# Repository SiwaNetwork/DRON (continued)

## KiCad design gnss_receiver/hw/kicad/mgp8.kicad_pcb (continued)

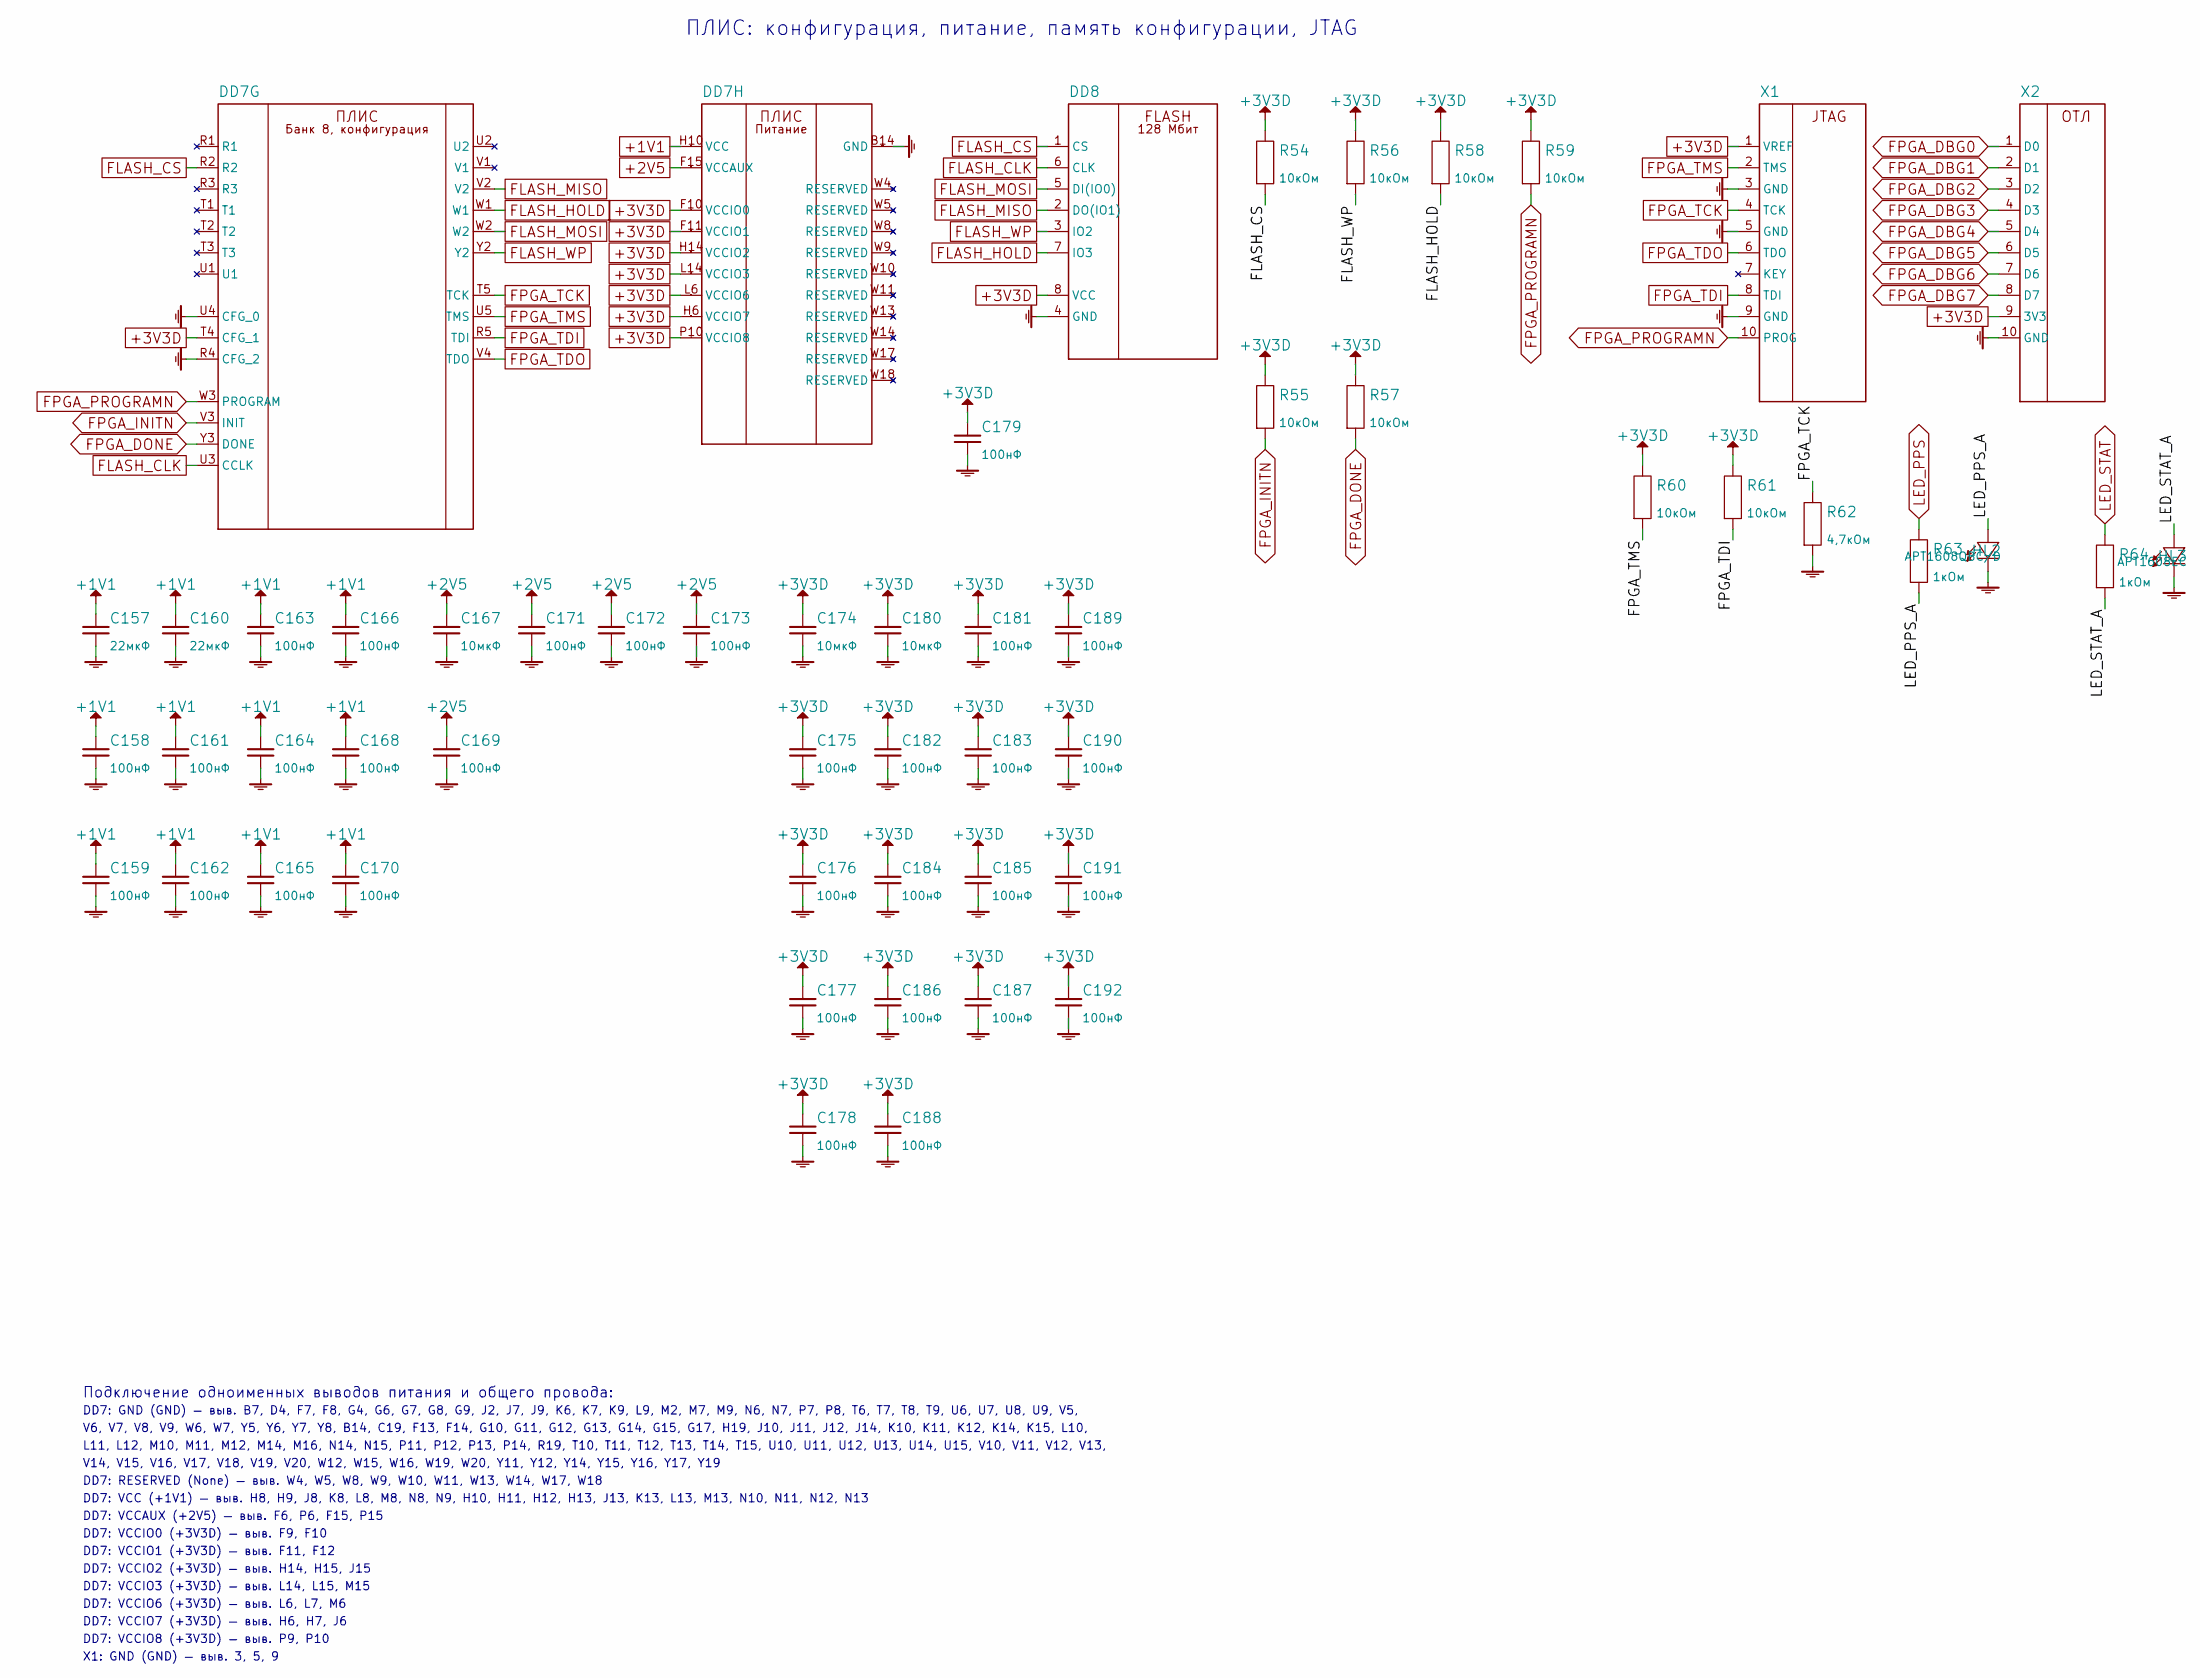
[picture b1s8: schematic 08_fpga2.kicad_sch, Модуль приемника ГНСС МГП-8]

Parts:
C157, C160: 22мкФ; C_0603_1608Metric
C158, C159, C161, C162, C163, C164, C165, C166, C168, C169, C170, C171, C172, C173, C175, C176, C177, C178, C179, C181, C182, C183, C184, C185, C186, C187, C188, C189, C190, C191, C192: 100нФ; C_0402_1005Metric
C167, C174, C180: 10мкФ; C_0603_1608Metric
DD7: LFE5U-45F-6BG381I; Lattice_caBGA-381_17x17mm_Layout20x20_P0.8mm
DD8: W25Q128JVSIQ; SOIC-8_5.3x5.3mm_P1.27mm
HL2: APT1608QBC/D; LED_0603_1608Metric
HL3: APT1608EC; LED_0603_1608Metric
R54, R55, R56, R57, R58, R59, R60, R61: 10кОм; R_0402_1005Metric
R62: 4,7кОм; R_0402_1005Metric
R63, R64: 1кОм; R_0402_1005Metric
X1, X2: FTSH-105-01-L-DV-K; PinHeader_2x05_P1.27mm_Vertical_SMD

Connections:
+1V1: C157.1, C158.1, C159.1, C160.1, C161.1, C162.1, C163.1, C164.1, C165.1, C166.1, C168.1, C170.1, DD7.H8, DD7.H9, DD7.H10 (VCC), DD7.H11, DD7.H12, DD7.H13, DD7.J8, DD7.J13, DD7.K8, DD7.K13, DD7.L8, DD7.L13, DD7.M8, DD7.M13, DD7.N8, DD7.N9, DD7.N10, DD7.N11, DD7.N12, DD7.N13; also elsewhere on the board
+2V5: C167.1, C169.1, C171.1, C172.1, C173.1, DD7.F6, DD7.F15 (VCCAUX), DD7.P6, DD7.P15; also elsewhere on the board
+3V3D: C174.1, C175.1, C176.1, C177.1, C178.1, C179.1, C180.1, C181.1, C182.1, C183.1, C184.1, C185.1, C186.1, C187.1, C188.1, C189.1, C190.1, C191.1, C192.1, DD7.F9, DD7.F10 (VCCIO0), DD7.F11 (VCCIO1), DD7.F12, DD7.H6 (VCCIO7), DD7.H7, DD7.H14 (VCCIO2), DD7.H15, DD7.J6, DD7.J15, DD7.L6 (VCCIO6), DD7.L7, DD7.L14 (VCCIO3), DD7.L15, DD7.M6, DD7.M15, DD7.P9, DD7.P10 (VCCIO8), DD7.T4 (CFG_1), DD8.8 (VCC), R54.1, R55.1, R56.1, R57.1, R58.1, R59.1, R60.1, R61.1, X1.1 (VREF), X2.9 (3V3); also elsewhere on the board
/Лист 8. ПЛИС: конфигурация, питание, память конфигурации, JTAG/LED_PPS_A: HL2.2, R63.2
/Лист 8. ПЛИС: конфигурация, питание, память конфигурации, JTAG/LED_STAT_A: HL3.2, R64.2
FLASH_CLK: DD7.U3 (CCLK), DD8.6 (CLK)
FLASH_CS: DD7.R2, DD8.1 (CS), R54.2
FLASH_HOLD: DD7.W1, DD8.7 (IO3), R58.2
FLASH_MISO: DD7.V2, DD8.2 (DO(IO1))
FLASH_MOSI: DD7.W2, DD8.5 (DI(IO0))
FLASH_WP: DD7.Y2, DD8.3 (IO2), R56.2
FPGA_DBG0: X2.1 (D0); also elsewhere on the board
FPGA_DBG1: X2.2 (D1); also elsewhere on the board
FPGA_DBG2: X2.3 (D2); also elsewhere on the board
FPGA_DBG3: X2.4 (D3); also elsewhere on the board
FPGA_DBG4: X2.5 (D4); also elsewhere on the board
FPGA_DBG5: X2.6 (D5); also elsewhere on the board
FPGA_DBG6: X2.7 (D6); also elsewhere on the board
FPGA_DBG7: X2.8 (D7); also elsewhere on the board
FPGA_DONE: DD7.Y3 (DONE), R57.2; also elsewhere on the board
FPGA_INITN: DD7.V3 (INIT), R55.2; also elsewhere on the board
FPGA_PROGRAMN: DD7.W3 (PROGRAM), R59.2, X1.10 (PROG); also elsewhere on the board
FPGA_TCK: DD7.T5 (TCK), R62.1, X1.4 (TCK)
FPGA_TDI: DD7.R5 (TDI), R61.2, X1.8 (TDI)
FPGA_TDO: DD7.V4 (TDO), X1.6 (TDO)
FPGA_TMS: DD7.U5 (TMS), R60.2, X1.2 (TMS)
GND: C157.2, C158.2, C159.2, C160.2, C161.2, C162.2, C163.2, C164.2, C165.2, C166.2, C167.2, C168.2, C169.2, C170.2, C171.2, C172.2, C173.2, C174.2, C175.2, C176.2, C177.2, C178.2, C179.2, C180.2, C181.2, C182.2, C183.2, C184.2, C185.2, C186.2, C187.2, C188.2, C189.2, C190.2, C191.2, C192.2, DD7.B7, DD7.B14 (GND), DD7.C19, DD7.D4, DD7.F7, DD7.F8, DD7.F13, DD7.F14, DD7.G4, DD7.G6, DD7.G7, DD7.G8, DD7.G9, DD7.G10, DD7.G11, DD7.G12, DD7.G13, DD7.G14, DD7.G15, DD7.G17, DD7.H19, DD7.J2, DD7.J7, DD7.J9, DD7.J10, DD7.J11, DD7.J12, DD7.J14, DD7.K6, DD7.K7, DD7.K9, DD7.K10, DD7.K11, DD7.K12, DD7.K14, DD7.K15, DD7.L9, DD7.L10, DD7.L11, DD7.L12, DD7.M2, DD7.M7, DD7.M9, DD7.M10, DD7.M11, DD7.M12, DD7.M14, DD7.M16, DD7.N6, DD7.N7, DD7.N14, DD7.N15, DD7.P7, DD7.P8, DD7.P11, DD7.P12, DD7.P13, DD7.P14, DD7.R4 (CFG_2), DD7.R19, DD7.T6, DD7.T7, DD7.T8, DD7.T9, DD7.T10, DD7.T11, DD7.T12, DD7.T13, DD7.T14, DD7.T15, DD7.U4 (CFG_0), DD7.U6, DD7.U7, DD7.U8, DD7.U9, DD7.U10, DD7.U11, DD7.U12, DD7.U13, DD7.U14, DD7.U15, DD7.V5, DD7.V6, DD7.V7, DD7.V8, DD7.V9, DD7.V10, DD7.V11, DD7.V12, DD7.V13, DD7.V14, DD7.V15, DD7.V16, DD7.V17, DD7.V18, DD7.V19, DD7.V20, DD7.W6, DD7.W7, DD7.W12, DD7.W15, DD7.W16, DD7.W19, DD7.W20, DD7.Y5, DD7.Y6, DD7.Y7, DD7.Y8, DD7.Y11, DD7.Y12, DD7.Y14, DD7.Y15, DD7.Y16, DD7.Y17, DD7.Y19, DD8.4 (GND), HL2.1, HL3.1, R62.2, X1.3 (GND), X1.5 (GND), X1.9 (GND), X2.10 (GND); also elsewhere on the board
LED_PPS: R63.1; also elsewhere on the board
LED_STAT: R64.1; also elsewhere on the board

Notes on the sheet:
ПЛИС: конфигурация, питание, память конфигурации, JTAG
Подключение одноименных выводов питания и общего провода:
DD7: GND (GND) — выв. B7, D4, F7, F8, G4, G6, G7, G8, G9, J2, J7, J9, K6, K7, K9, L9, M2, M7, M9, N6, N7, P7, P8, T6, T7, T8, T9, U6, U7, U8, U9, V5,
V6, V7, V8, V9, W6, W7, Y5, Y6, Y7, Y8, B14, C19, F13, F14, G10, G11, G12, G13, G14, G15, G17, H19, J10, J11, J12, J14, K10, K11, K12, K14, K15, L10,
L11, L12, M10, M11, M12, M14, M16, N14, N15, P11, P12, P13, P14, R19, T10, T11, T12, T13, T14, T15, U10, U11, U12, U13, U14, U15, V10, V11, V12, V13,
V14, V15, V16, V17, V18, V19, V20, W12, W15, W16, W19, W20, Y11, Y12, Y14, Y15, Y16, Y17, Y19
DD7: RESERVED (None) — выв. W4, W5, W8, W9, W10, W11, W13, W14, W17, W18
DD7: VCC (+1V1) — выв. H8, H9, J8, K8, L8, M8, N8, N9, H10, H11, H12, H13, J13, K13, L13, M13, N10, N11, N12, N13
DD7: VCCAUX (+2V5) — выв. F6, P6, F15, P15
DD7: VCCIO0 (+3V3D) — выв. F9, F10
DD7: VCCIO1 (+3V3D) — выв. F11, F12
DD7: VCCIO2 (+3V3D) — выв. H14, H15, J15
DD7: VCCIO3 (+3V3D) — выв. L14, L15, M15
DD7: VCCIO6 (+3V3D) — выв. L6, L7, M6
DD7: VCCIO7 (+3V3D) — выв. H6, H7, J6
DD7: VCCIO8 (+3V3D) — выв. P9, P10
X1: GND (GND) — выв. 3, 5, 9

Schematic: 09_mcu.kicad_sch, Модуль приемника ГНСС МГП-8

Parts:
C193, C194: 10пФ; C_0402_1005Metric
C195, C196, C197, C199, C200, C203, C205, C206, C208, C209: 100нФ; C_0402_1005Metric
C198: 1мкФ; C_0402_1005Metric
C201, C202: 2,2мкФ; C_0402_1005Metric
C204: 4,7мкФ; C_0402_1005Metric
C207: 10мкФ; C_0603_1608Metric
DA24: MCP2562FD-E/SN; SOIC-8_3.9x4.9mm_P1.27mm
DD9: STM32H743VIT6; LQFP-100_14x14mm_P0.5mm
HL4: APT1608SGC; LED_0603_1608Metric
HL5: APT1608YC; LED_0603_1608Metric
L12: 220Ом; L_0603_1608Metric
R65: 33Ом; R_0402_1005Metric
R66, R68, R69, R70, R71, R72: 47кОм; R_0402_1005Metric
R67, R73: 10кОм; R_0402_1005Metric
R74, R75: 1кОм; R_0402_1005Metric
R76: 120Ом; R_0402_1005Metric; not fitted
VD7: NUP2105LT1G; SOT-23
X3: FTSH-105-01-L-DV-K; PinHeader_2x05_P1.27mm_Vertical_SMD
XS1: DM3AT-SF-PEJM5; microSD_HC_Hirose_DM3AT-SF-PEJM5
ZQ1: 32,768кГц; Crystal_SMD_3215-2Pin_3.2x1.5mm

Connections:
+3V3D: C196.1, C197.1, C199.1, C200.1, C204.1, C205.1, C206.1, C207.1, C209.1, DA24.5 (Vio), DD9.6 (VBAT), DD9.11, DD9.27, DD9.50, DD9.75, DD9.100 (VDD), L12.1, R66.1, R68.1, R69.1, R70.1, R71.1, R72.1, R73.1, R74.1, R75.1, X3.1 (VREF), XS1.4 (VDD); also elsewhere on the board
+5V_SYS: C208.1, DA24.3 (VDD); also elsewhere on the board
/Лист 9. Управляющий микроконтроллер, microSD, CAN FD/LED_ANT_A: HL5.2, R75.2
/Лист 9. Управляющий микроконтроллер, microSD, CAN FD/LED_FIX_A: HL4.2, R74.2
ANT_EN: DD9.5 (PE6); also elsewhere on the board
ANT_IMON: DD9.15 (PC0); also elsewhere on the board
CAN_H: DA24.7 (CANH), R76.1, VD7.1 (K); also elsewhere on the board
CAN_L: DA24.6 (CANL), R76.2, VD7.2 (K); also elsewhere on the board
CAN_RX: DA24.4 (RXD), DD9.95 (PB8)
CAN_STBY: DA24.8 (STBY), DD9.51 (PB12), R73.2
CAN_TX: DA24.1 (TXD), DD9.96 (PB9)
DBG_RX: DD9.23 (PA1); also elsewhere on the board
DBG_TX: DD9.22 (PA0); also elsewhere on the board
EXTINT_MCU: DD9.25 (PA3); also elsewhere on the board
FMC_DA0: DD9.61 (PD14); also elsewhere on the board
FMC_DA1: DD9.62 (PD15); also elsewhere on the board
FMC_DA2: DD9.81 (PD0); also elsewhere on the board
FMC_DA3: DD9.82 (PD1); also elsewhere on the board
FMC_DA4: DD9.37 (PE7); also elsewhere on the board
FMC_DA5: DD9.38 (PE8); also elsewhere on the board
FMC_DA6: DD9.39 (PE9); also elsewhere on the board
FMC_DA7: DD9.40 (PE10); also elsewhere on the board
FMC_DA8: DD9.41 (PE11); also elsewhere on the board
FMC_DA9: DD9.42 (PE12); also elsewhere on the board
FMC_DA10: DD9.43 (PE13); also elsewhere on the board
FMC_DA11: DD9.44 (PE14); also elsewhere on the board
FMC_DA12: DD9.45 (PE15); also elsewhere on the board
FMC_DA13: DD9.55 (PD8); also elsewhere on the board
FMC_DA14: DD9.56 (PD9); also elsewhere on the board
FMC_DA15: DD9.57 (PD10); also elsewhere on the board
FMC_NE1: DD9.88 (PD7); also elsewhere on the board
FMC_NL: DD9.93 (PB7); also elsewhere on the board
FMC_NOE: DD9.85 (PD4); also elsewhere on the board
FMC_NWAIT: DD9.87 (PD6); also elsewhere on the board
FMC_NWE: DD9.86 (PD5); also elsewhere on the board
FPGA_DONE: DD9.3 (PE4); also elsewhere on the board
FPGA_INITN: DD9.2 (PE3); also elsewhere on the board
FPGA_IRQ: DD9.4 (PE5); also elsewhere on the board
FPGA_PROGRAMN: DD9.1 (PE2); also elsewhere on the board
FX3_RESETN: DD9.36 (PB2); also elsewhere on the board
GND: C193.2, C194.2, C195.2, C196.2, C197.2, C198.2, C199.2, C200.2, C201.2, C202.2, C203.2, C204.2, C205.2, C206.2, C207.2, C208.2, C209.2, DA24.2 (VSS), DD9.10 (VSS), DD9.19 (VSSA), DD9.26, DD9.49, DD9.74, DD9.99, R67.2, VD7.3 (A), X3.3 (GND), X3.5 (GND), X3.9 (GND), XS1.6 (VSS), XS1.9 (DET_B), XS1.11 (SHIELD); also elsewhere on the board
GPS_RX: DD9.69 (PA10); also elsewhere on the board
GPS_SCL: DD9.59 (PD12); also elsewhere on the board
GPS_SDA: DD9.60 (PD13); also elsewhere on the board
GPS_TX: DD9.68 (PA9); also elsewhere on the board
LED_ANT_K: DD9.53 (PB14), HL5.1
LED_FIX_K: DD9.7 (PC13), HL4.1
MCU_BOOT0: DD9.94 (BOOT0), R67.1
MCU_CLK24: DD9.12 (PH0); also elsewhere on the board
MCU_NRST: C195.1, DD9.14 (NRST), X3.10 (RST)
MCU_TDI: DD9.77 (PA15), X3.8 (TDI)
OSC32_IN: C193.1, DD9.8 (PC14), ZQ1.1
OSC32_OUT: C194.1, DD9.9 (PC15), ZQ1.2
PPS_MCU: DD9.24 (PA2); also elsewhere on the board
SD_CD: DD9.52 (PB13), R72.2, XS1.10 (DET_A)
SD_CLK: R65.2, XS1.5 (CLK)
SD_CLK_R: DD9.80 (PC12), R65.1
SD_CMD: DD9.83 (PD2), R69.2, XS1.3 (CMD)
SD_D0: DD9.65 (PC8), R68.2, XS1.7 (DAT0)
SD_D1: DD9.66 (PC9), R70.2, XS1.8 (DAT1)
SD_D2: DD9.78 (PC10), R71.2, XS1.1 (DAT2)
SD_D3: DD9.79 (PC11), R66.2, XS1.2 (DAT3/CD)
SWCLK: DD9.76 (PA14), X3.4 (SWCLK)
SWDIO: DD9.72 (PA13), X3.2 (SWDIO)
SWO: DD9.89 (PB3), X3.6 (SWO)
V1V1_MON: DD9.33 (PC5); also elsewhere on the board
V3V3_MON: DD9.32 (PC4); also elsewhere on the board
V5_MON: DD9.16 (PC1); also elsewhere on the board
VCAP: C201.1, C202.1, DD9.48 (VCAP), DD9.73
VDDA: C198.1, C203.1, DD9.20 (VREF+), DD9.21 (VDDA), L12.2

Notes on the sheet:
Управляющий микроконтроллер, microSD, CAN FD
Подключение одноименных выводов питания и общего провода:
DD9: VCAP (VCAP) — выв. 48, 73
DD9: VDD (+3V3D) — выв. 11, 27, 50, 75, 100
DD9: VSS (GND) — выв. 10, 26, 49, 74, 99
X3: GND (GND) — выв. 3, 5, 9

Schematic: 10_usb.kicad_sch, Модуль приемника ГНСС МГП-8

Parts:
C210, C229: 22мкФ; C_0603_1608Metric
C211, C212, C214, C215, C218, C219, C220, C221, C222, C225, C227, C230, C231, C232, C233, C234, C235: 100нФ; C_0402_1005Metric
C213, C216: 13пФ; C_0402_1005Metric
C217: 1мкФ; C_0402_1005Metric
C223, C228: 10нФ; C_0402_1005Metric
C224, C226: 10мкФ; C_0603_1608Metric
DA25: SPX3819M5-L-3-3/TR; SOT-23-5
DA26: TPS62130RGTR; VQFN-16-1EP_3x3mm_P0.5mm_EP1.68x1.68mm_ThermalVias
DA27: USBLC6-2SC6; SOT-23-6
DD10: CYUSB3014-BZXI; BGA-121
DD11: PI3USB302-AZBEX; 20TQFN-ZB_PI3USB302-A_DIO
DD12: AT24CM01-XHM-T; TSSOP_8P
HL6: APT1608YC; LED_0603_1608Metric
HL7: APT1608SGC; LED_0603_1608Metric
L13: 2,2мкГн; L_Coilcraft_XxL4020
R77: 6,04кОм; R_0402_1005Metric
R78, R80, R82, R87: 10кОм; R_0402_1005Metric
R79: 200Ом; R_0402_1005Metric
R81, R91: 100кОм; R_0402_1005Metric
R83, R84: 1кОм; R_0402_1005Metric
R85, R86: 2,2кОм; R_0402_1005Metric
R88, R89: 5,1кОм; R_0402_1005Metric
R90: 49,9кОм; R_0402_1005Metric
X4: M22-2510205; PinHeader_1x02_P2.00mm_Vertical
XS2: USB4080-03-A; USB4080-03-A_GCT
ZQ2: 19,2МГц; XTAL_SMD

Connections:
+1V2_FX3: C210.1, C211.1, C212.1, C214.1, C215.1, C218.1, C219.1, DA26.14 (VOS), DD10.A2 (U3RXVDDQ), DD10.A7 (AVDD), DD10.B5 (U3TXVDDQ), DD10.B10 (VDD), DD10.C3, DD10.E9, DD10.F11, DD10.H1, DD10.J11, DD10.L5, DD10.L7, L13.2, R90.1
+3V3_FX3: C222.1, C225.1, C229.1, C230.1, C231.1, C232.1, C233.1, C234.1, C235.1, DA25.5 (OUT), DD10.B1 (VIO4), DD10.B6 (CVDDQ), DD10.C11 (VIO5), DD10.E3 (VIO3), DD10.F1 (VIO2), DD10.H11 (VIO1), DD10.L9, DD11.1 (VDD), DD11.6, DD11.10, DD12.8 (VCC), R78.1, R81.1, R82.1, R83.1, R84.1, R85.1, R86.1, X4.1 (3V3)
+5V_USB: C224.1, C226.1, C227.1, DA25.1 (IN), DA25.3 (EN), DA26.10 (VIN), DA26.11, DA26.12, DA26.13 (EN), DA27.5 (VBUS), DD10.E10 (VBATT), DD10.E11 (VBUS), XS2.A4 (VBUS), XS2.A9, XS2.B4, XS2.B9; also elsewhere on the board
/Лист 10. Контроллер USB 3.0 (режим выдачи отсчетов ПЧ)/FX3_LED1_A: HL7.2, R83.2
/Лист 10. Контроллер USB 3.0 (режим выдачи отсчетов ПЧ)/FX3_LED2_A: HL6.2, R84.2
EEPROM_A: DD12.1 (A0), DD12.2 (A1), R87.1, X4.2 (A)
FB_1V2_FX3: DA26.5 (FB), R90.2, R91.1
FX3_BP33: C223.1, DA25.4 (BP)
FX3_CSN_A: DD10.K8 (GPIO[17]); also elsewhere on the board
FX3_CSN_B: DD10.K7 (GPIO[18]); also elsewhere on the board
FX3_CSN_C: DD10.J7 (GPIO[19]); also elsewhere on the board
FX3_CSN_D: DD10.H7 (GPIO[20]); also elsewhere on the board
FX3_CSN_E: DD10.G7 (GPIO[21]); also elsewhere on the board
FX3_CSN_F: DD10.G6 (GPIO[22]); also elsewhere on the board
FX3_CSN_G: DD10.K6 (GPIO[23]); also elsewhere on the board
FX3_CSN_H: DD10.H8 (GPIO[24]); also elsewhere on the board
FX3_G0: DD10.F10 (GPIO[0]); also elsewhere on the board
FX3_G1: DD10.F9 (GPIO[1]); also elsewhere on the board
FX3_G2: DD10.F7 (GPIO[2]); also elsewhere on the board
FX3_G3: DD10.G10 (GPIO[3]); also elsewhere on the board
FX3_G4: DD10.G9 (GPIO[4]); also elsewhere on the board
FX3_G5: DD10.F8 (GPIO[5]); also elsewhere on the board
FX3_G6: DD10.H10 (GPIO[6]); also elsewhere on the board
FX3_G7: DD10.H9 (GPIO[7]); also elsewhere on the board
FX3_G8: DD10.J10 (GPIO[8]); also elsewhere on the board
FX3_G9: DD10.J9 (GPIO[9]); also elsewhere on the board
FX3_G10: DD10.K11 (GPIO[10]); also elsewhere on the board
FX3_G11: DD10.L10 (GPIO[11]); also elsewhere on the board
FX3_G12: DD10.K10 (GPIO[12]); also elsewhere on the board
FX3_G13: DD10.K9 (GPIO[13]); also elsewhere on the board
FX3_G14: DD10.J8 (GPIO[14]); also elsewhere on the board
FX3_G15: DD10.G8 (GPIO[15]); also elsewhere on the board
FX3_G33: DD10.K2 (GPIO[33]); also elsewhere on the board
FX3_G34: DD10.J4 (GPIO[34]); also elsewhere on the board
FX3_G35: DD10.K1 (GPIO[35]); also elsewhere on the board
FX3_G36: DD10.J2 (GPIO[36]); also elsewhere on the board
FX3_G37: DD10.J3 (GPIO[37]); also elsewhere on the board
FX3_G38: DD10.J1 (GPIO[38]); also elsewhere on the board
FX3_G39: DD10.H2 (GPIO[39]); also elsewhere on the board
FX3_G40: DD10.H3 (GPIO[40]); also elsewhere on the board
FX3_G41: DD10.F4 (GPIO[41]/A0); also elsewhere on the board
FX3_G42: DD10.G2 (GPIO[42]/A1); also elsewhere on the board
FX3_G43: DD10.G3 (GPIO[43]); also elsewhere on the board
FX3_G44: DD10.F3 (GPIO[44]); also elsewhere on the board
FX3_G46: DD10.F5 (GPIO[46]); also elsewhere on the board
FX3_G47: DD10.E1 (GPIO[47]); also elsewhere on the board
FX3_G48: DD10.E5 (GPIO[48]); also elsewhere on the board
FX3_G49: DD10.E4 (GPIO[49]); also elsewhere on the board
FX3_LED1: DD10.K5 (GPIO[27]), HL7.1
FX3_LED2: DD10.J5 (GPIO[28]), HL6.1
FX3_LOCK_A: DD10.D1 (GPIO[50]); also elsewhere on the board
FX3_LOCK_B: DD10.D2 (GPIO[51]); also elsewhere on the board
FX3_LOCK_C: DD10.D3 (GPIO[52]); also elsewhere on the board
FX3_LOCK_D: DD10.D4 (GPIO[53]); also elsewhere on the board
FX3_LOCK_E: DD10.C1 (GPIO[54]); also elsewhere on the board
FX3_LOCK_F: DD10.C2 (GPIO[55]); also elsewhere on the board
FX3_LOCK_G: DD10.D5 (GPIO[56]); also elsewhere on the board
FX3_LOCK_H: DD10.C4 (GPIO[57]); also elsewhere on the board
FX3_PCLK: DD10.J6 (GPIO[16]); also elsewhere on the board
FX3_PMODE1: DD10.H4 (GPIO[31]), R78.2
FX3_PWR_OK: DA26.4 (PG), R82.2; also elsewhere on the board
FX3_RESETN: C217.1, DD10.C5 (RESET#), R81.2; also elsewhere on the board
FX3_RUSB2: DD10.C8 (R_USB2), R77.1
FX3_RUSB3: DD10.B3 (R_USB3), R79.1
FX3_SCL: DD10.D9 (I2C_GPIO[58]), DD12.6 (SCL), R86.2
FX3_SCLK: DD10.G5 (GPIO[25]); also elsewhere on the board
FX3_SDA: DD10.D10 (I2C_GPIO[59]), DD12.5 (SDA), R85.2
FX3_SDATA: DD10.H6 (GPIO[26]); also elsewhere on the board
FX3_XI: C213.1, DD10.C6 (XTALIN), ZQ2.3
FX3_XO: C216.1, DD10.C7 (XTALOUT), ZQ2.1
GND: C210.2, C211.2, C212.2, C213.2, C214.2, C215.2, C216.2, C217.2, C218.2, C219.2, C222.2, C223.2, C224.2, C225.2, C226.2, C227.2, C228.2, C229.2, C230.2, C231.2, C232.2, C233.2, C234.2, C235.2, DA25.2 (GND), DA26.6, DA26.7 (FSW), DA26.8 (DEF), DA26.15 (GND), DA26.16, DA26.17, DA27.2 (GND), DD10.A1 (U3VSSQ), DD10.A8 (VSS), DD10.B2 (FSLC[0]), DD10.B4 (FSLC[1]), DD10.B7 (AVSS), DD10.B8, DD10.B9, DD10.D8, DD10.E2, DD10.E6 (FSLC[2]), DD10.G1, DD10.G11, DD10.K3, DD10.K4, DD10.L1, DD10.L2, DD10.L3, DD10.L6, DD10.L11, DD11.2 (PD), DD11.5, DD11.11 (GND), DD11.20, DD11.21, DD12.3 (A2), DD12.4 (GND), DD12.7 (WP), R77.2, R79.2, R80.2, R87.2, R88.2, R89.2, R91.2, XS2.A1 (GND), XS2.A12, XS2.B1, XS2.B12, XS2.EP, ZQ2.2, ZQ2.4; also elsewhere on the board
SSRXN1: DD11.12 (RX2-), XS2.B10 (SSRXN1)
SSRXN2: DD11.16 (RX1-), XS2.A10 (SSRXN2)
SSRXP1: DD11.13 (RX2+), XS2.B11 (SSRXP1)
SSRXP2: DD11.17 (RX1+), XS2.A11 (SSRXP2)
SSRX_N: DD10.A3 (SSRXM), DD11.8 (RX-)
SSRX_P: DD10.A4 (SSRXP), DD11.7 (RX+)
SSTXN1: DD11.14 (TX2-), XS2.A3 (SSTXN1)
SSTXN2: DD11.18 (TX1-), XS2.B3 (SSTXN2)
SSTXP1: DD11.15 (TX2+), XS2.A2 (SSTXP1)
SSTXP2: DD11.19 (TX1+), XS2.B2 (SSTXP2)
SSTX_N: C221.2, DD11.4 (TX-)
SSTX_N_C: C221.1, DD10.A6 (SSTXM)
SSTX_P: C220.2, DD11.3 (TX+)
SSTX_P_C: C220.1, DD10.A5 (SSTXP)
SS_1V2_FX3: C228.1, DA26.9 (SS/TR)
SW_1V2_FX3: DA26.1 (SW), DA26.2, DA26.3, L13.1
USB3_PORT_SEL: DD10.F2 (GPIO[45]), DD11.9 (SEL), R80.1
USB_CC1: R88.1, XS2.A5 (CC1)
USB_CC2: R89.1, XS2.B5 (CC2)
USB_DM: DA27.3 (I/O2), DA27.4 (I/O2), DD10.A10 (DM), XS2.A7 (DN1), XS2.B7 (DN2)
USB_DP: DA27.1 (I/O1), DA27.6 (I/O1), DD10.A9 (DP), XS2.A6 (DP1), XS2.B6 (DP2)

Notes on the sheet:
Контроллер USB 3.0 (режим выдачи отсчетов ПЧ)
Подключение одноименных выводов питания и общего провода:
DA26: GND (GND) — выв. 6, 15, 16, 17
DA26: SW (SW_1V2_FX3) — выв. 1, 2, 3
DA26: VIN (+5V_USB) — выв. 10, 11, 12
DA27: I/O1 (USB_DP) — выв. 1, 6
DA27: I/O2 (USB_DM) — выв. 3, 4
DD10: VDD (+1V2_FX3) — выв. C3, E9, H1, L5, L7, B10, F11, J11
DD10: VIO1 (+3V3_FX3) — выв. L9, H11
DD10: VSS (GND) — выв. A8, B8, B9, D8, E2, G1, K3, K4, L1, L2, L3, L6, G11, L11
DD11: GND (GND) — выв. 5, 11, 20, 21
DD11: VDD (+3V3_FX3) — выв. 1, 6, 10
XS2: GND (GND) — выв. A1, B1, A12, B12
XS2: VBUS (+5V_USB) — выв. A4, A9, B4, B9

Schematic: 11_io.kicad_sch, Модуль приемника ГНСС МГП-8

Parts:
DA28, DA29, DA30: USBLC6-2SC6; SOT-23-6
R92, R93: 100Ом; R_0402_1005Metric
R94, R95: 2,2кОм; R_0402_1005Metric; not fitted
X5: SM06B-GHS-TB; JST_GH_SM06B-GHS-TB_1x06-1MP_P1.25mm_Horizontal
X6, X7: SM04B-GHS-TB; JST_GH_SM04B-GHS-TB_1x04-1MP_P1.25mm_Horizontal
X8: SM04B-SRSS-TB; JST_SH_SM04B-SRSS-TB_1x04-1MP_P1.00mm_Horizontal

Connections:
+3V3D: DA28.5 (VBUS), DA29.5 (VBUS), DA30.5 (VBUS), R94.1, R95.1, X8.1 (3V3); also elsewhere on the board
+5V_CAN: X7.1 (+5V); also elsewhere on the board
+5V_GPS: X5.1 (+5V); also elsewhere on the board
CAN_H: X7.2 (CANH); also elsewhere on the board
CAN_L: X7.3 (CANL); also elsewhere on the board
DBG_RX: X8.3 (RX); also elsewhere on the board
DBG_TX: X8.2 (TX); also elsewhere on the board
EXTINT_IN: DA30.3 (I/O2), DA30.4 (I/O2), X6.2 (EXT); also elsewhere on the board
GND: DA28.2 (GND), DA29.2 (GND), DA30.2 (GND), X5.6 (GND), X6.3 (GND), X6.4 (GND), X7.4 (GND), X8.4 (GND); also elsewhere on the board
GPS_P_RX: DA28.1 (I/O1), DA28.6 (I/O1), R92.1, X5.2 (RX)
GPS_P_TX: DA28.3 (I/O2), DA28.4 (I/O2), R93.1, X5.3 (TX)
GPS_RX: R92.2; also elsewhere on the board
GPS_SCL: DA29.1 (I/O1), DA29.6 (I/O1), R94.2, X5.4 (SCL); also elsewhere on the board
GPS_SDA: DA29.3 (I/O2), DA29.4 (I/O2), R95.2, X5.5 (SDA); also elsewhere on the board
GPS_TX: R93.2; also elsewhere on the board
PPS_PORT: DA30.1 (I/O1), DA30.6 (I/O1), X6.1 (1PPS); also elsewhere on the board

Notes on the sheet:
Внешние интерфейсы
Подключение одноименных выводов питания и общего провода:
DA28: I/O1 (GPS_P_RX) — выв. 1, 6
DA28: I/O2 (GPS_P_TX) — выв. 3, 4
DA29: I/O1 (GPS_SCL) — выв. 1, 6
DA29: I/O2 (GPS_SDA) — выв. 3, 4
DA30: I/O1 (PPS_PORT) — выв. 1, 6
DA30: I/O2 (EXTINT_IN) — выв. 3, 4
X6: GND (GND) — выв. 3, 4

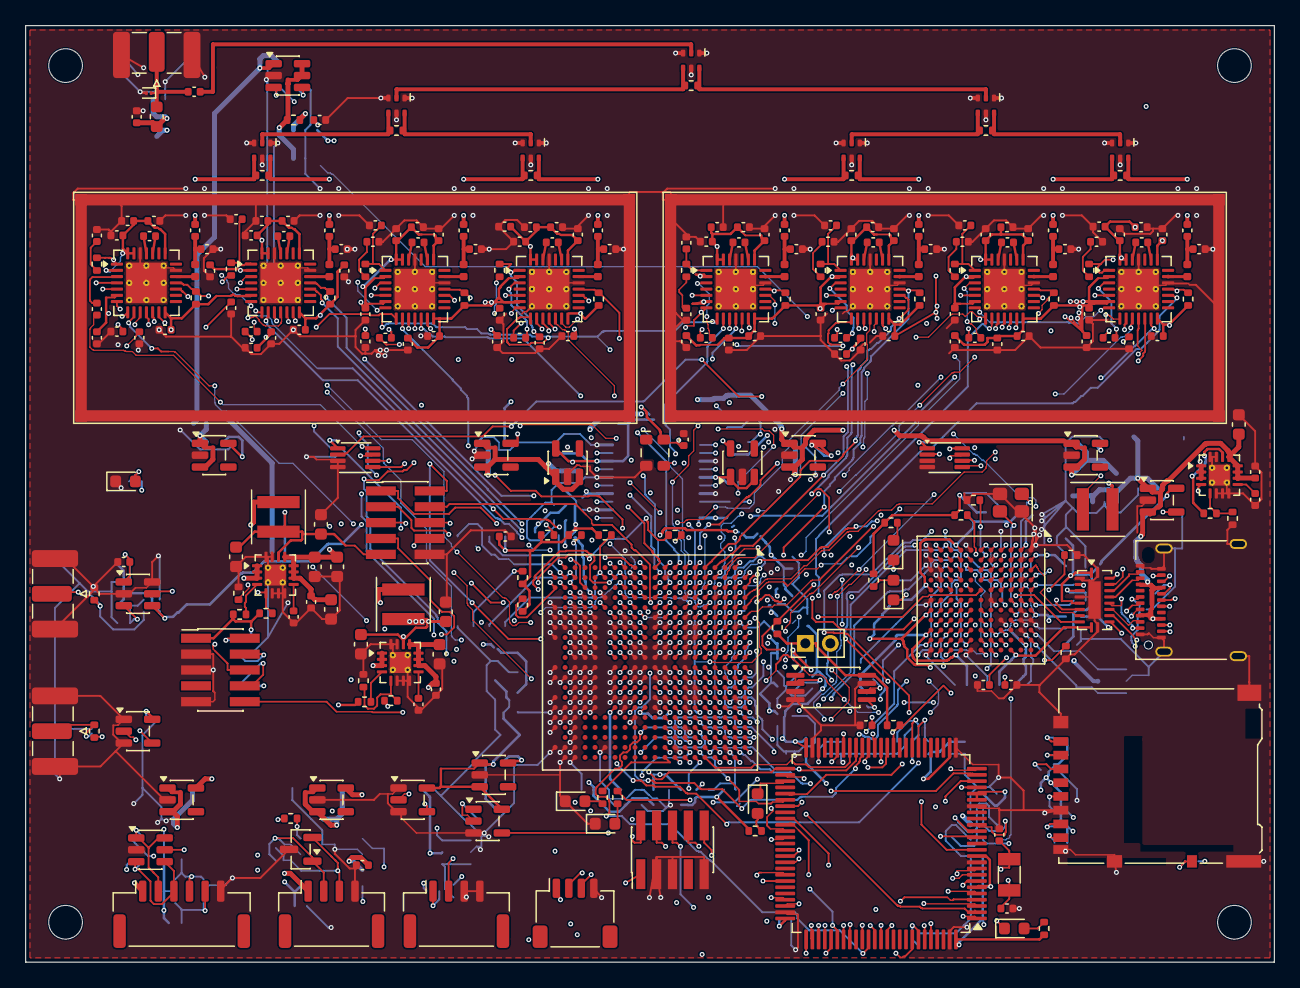
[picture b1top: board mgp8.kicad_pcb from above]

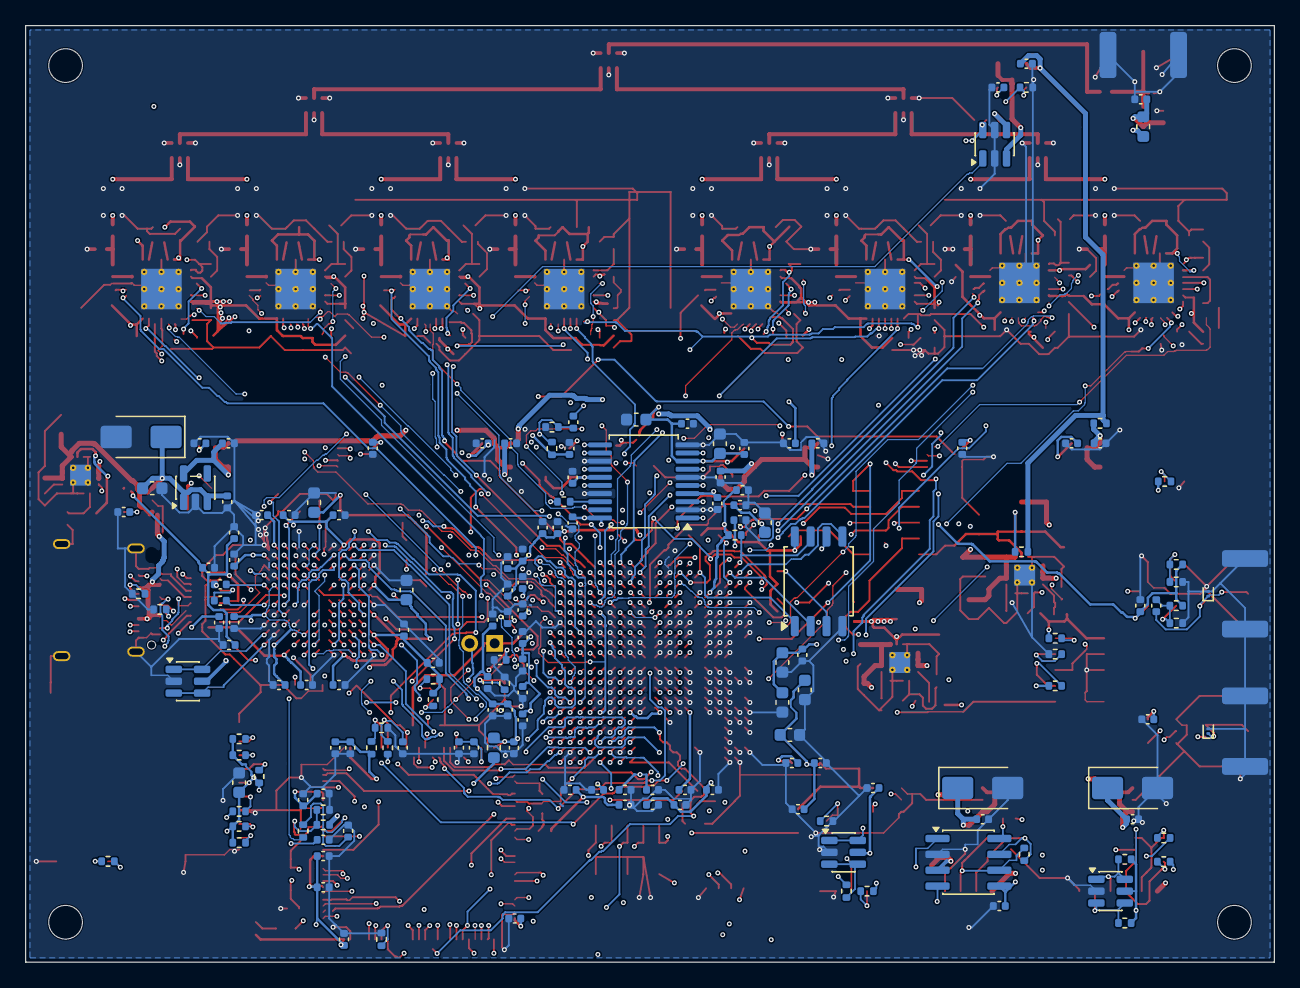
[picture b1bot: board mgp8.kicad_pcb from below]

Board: 8 copper layers, 100.0 x 75.0 mm, 429 parts (161 on the bottom side), 373 nets.

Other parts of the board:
H1, H2, H3, H4: MountingHole_2.7mm_M2.5
SH1, SH2: MS448-10F; SHIELD_MS448-10F

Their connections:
GND: SH1.1, SH2.1; also elsewhere on the board

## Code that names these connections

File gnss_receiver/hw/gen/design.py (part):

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    s = d.sheet("mcu", "Управляющий микроконтроллер, microSD, CAN FD", paper="A2")
    mcu = ics.stm32h743()
    mc = {f"#{n}": None for n in mcu.all_pins}
    fmc = {"PD14": 0, "PD15": 1, "PD0": 2, "PD1": 3, "PE7": 4, "PE8": 5, "PE9": 6, "PE10": 7, "PE11": 8,
           "PE12": 9, "PE13": 10, "PE14": 11, "PE15": 12, "PD8": 13, "PD9": 14, "PD10": 15}
    for pin, k in fmc.items():
        mc[pin] = f"FMC_DA{k}"
    mc.update({"PD4": "FMC_NOE", "PD5": "FMC_NWE", "PD7": "FMC_NE1", "PB7": "FMC_NL", "PD6": "FMC_NWAIT",
               "PH0": "MCU_CLK24", "PH1": None,
               "PA9": "GPS_TX", "PA10": "GPS_RX", "PD12": "GPS_SCL", "PD13": "GPS_SDA",
               "PA0": "DBG_TX", "PA1": "DBG_RX", "PA2": "PPS_MCU", "PA3": "EXTINT_MCU",
               "PB8": "CAN_RX", "PB9": "CAN_TX", "PB12": "CAN_STBY", "PB13": "SD_CD",
               "PC8": "SD_D0", "PC9": "SD_D1", "PC10": "SD_D2", "PC11": "SD_D3", "PC12": "SD_CLK_R", "PD2": "SD_CMD",
               "PC0": "ANT_IMON", "PC1": "V5_MON", "PC4": "V3V3_MON", "PC5": "V1V1_MON",
               "PE2": "FPGA_PROGRAMN", "PE3": "FPGA_INITN", "PE4": "FPGA_DONE", "PE5": "FPGA_IRQ",
               "PE6": "ANT_EN", "PB2": "FX3_RESETN", "PC13": "LED_FIX_K", "PB14": "LED_ANT_K",
               "PA13": "SWDIO", "PA14": "SWCLK", "PB3": "SWO", "PA15": "MCU_TDI",
               "PC14": "OSC32_IN", "PC15": "OSC32_OUT",
               "NRST": "MCU_NRST", "BOOT0": "MCU_BOOT0", "VBAT": "+3V3D", "VREF+": "VDDA", "VDDA": "VDDA",
               "VSSA": GND, "VDD": "+3V3D", "VCAP": "VCAP", "VSS": GND})
    s.add(mcu, mc, "mcu", units={1: "mcu", 2: "mcu", 3: "mcu"})
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    for k, c in enumerate(CH):
        gpio_net[17 + k] = f"FX3_CSN_{c}"
        gpio_net[50 + k] = f"FX3_LOCK_{c}"
    gpio_net.update({16: "FX3_PCLK", 25: "FX3_SCLK", 26: "FX3_SDATA", 27: "FX3_LED1", 28: "FX3_LED2",
                     29: None, 30: None, 31: "FX3_PMODE1", 32: None, 45: "USB3_PORT_SEL"})
    for name, nums in fx.pins.items():
        import re as _re
        m = _re.fullmatch(r"(?:I2C_)?GPIO\[(\d+)\](?:/A\d)?", name)
        if m and int(m.group(1)) in gpio_net:
            fc[name] = gpio_net[int(m.group(1))]
    fc.update({"I2C_GPIO[58]": "FX3_SCL", "I2C_GPIO[59]": "FX3_SDA", "O[60]": None,
               "DP": "USB_DP", "DM": "USB_DM", "SSTXP": "SSTX_P_C", "SSTXM": "SSTX_N_C", "SSRXP": "SSRX_P",
               "SSRXM": "SSRX_N", "OTG_ID": None, "R_USB2": "FX3_RUSB2", "R_USB3": "FX3_RUSB3",
               "XTALIN": "FX3_XI", "XTALOUT": "FX3_XO", "CLKIN": None, "CLKIN_32": None,
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    s.add(R("5.1k"), {"1": "USB_CC2", "2": GND}, "usbc")
    s.add(ics.usblc6(), {"#1": "USB_DP", "#6": "USB_DP", "#3": "USB_DM", "#4": "USB_DM", "VBUS": "+5V_USB",
                         "GND": GND}, "usbc")
    s.add(ics.pi3usb302(), {"TX+": "SSTX_P", "TX-": "SSTX_N", "RX+": "SSRX_P", "RX-": "SSRX_N",
                            "SEL": "USB3_PORT_SEL", "PD": GND, "VDD": "+3V3_FX3", "GND": GND,
                            "TX1+": "SSTXP2", "TX1-": "SSTXN2", "RX1+": "SSRXP2", "RX1-": "SSRXN2",
                            "TX2+": "SSTXP1", "TX2-": "SSTXN1", "RX2+": "SSRXP1", "RX2-": "SSRXN1"}, "mux")
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
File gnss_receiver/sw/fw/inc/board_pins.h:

/* МГП-8: выводы МК STM32H743VIT6 (DD9) по схеме ШИВА.468157.001 Э3, лист 9.
 * Создан tools/gen_board.py из hw/kicad/09_mcu.kicad_sch — не править вручную;
 * сверка со схемой — make -C sw/fw board-check. PIN(порт, n): порт A = 0 … K = 10. */
#ifndef BOARD_PINS_H
#define BOARD_PINS_H

#define PIN(port, n)   ((PORT_##port << 4) | (n))
#define PIN_PORT(p)    ((p) >> 4)
#define PIN_NUM(p)     ((p) & 15)
enum { PORT_A, PORT_B, PORT_C, PORT_D, PORT_E, PORT_F, PORT_G, PORT_H, PORT_I, PORT_J, PORT_K };

#define PIN_DBG_TX         PIN(A,  0)   /* вывод 22 */
#define PIN_DBG_RX         PIN(A,  1)   /* вывод 23 */
#define PIN_PPS_MCU        PIN(A,  2)   /* вывод 24 */
#define PIN_EXTINT_MCU     PIN(A,  3)   /* вывод 25 */
#define PIN_GPS_TX         PIN(A,  9)   /* вывод 68 */
#define PIN_GPS_RX         PIN(A, 10)   /* вывод 69 */
#define PIN_SWDIO          PIN(A, 13)   /* вывод 72 */
#define PIN_SWCLK          PIN(A, 14)   /* вывод 76 */
#define PIN_MCU_TDI        PIN(A, 15)   /* вывод 77 */
#define PIN_FX3_RESETN     PIN(B,  2)   /* вывод 36 */
#define PIN_SWO            PIN(B,  3)   /* вывод 89 */
#define PIN_FMC_NL         PIN(B,  7)   /* вывод 93 */
#define PIN_CAN_RX         PIN(B,  8)   /* вывод 95 */
#define PIN_CAN_TX         PIN(B,  9)   /* вывод 96 */
#define PIN_CAN_STBY       PIN(B, 12)   /* вывод 51 */
#define PIN_SD_CD          PIN(B, 13)   /* вывод 52 */
#define PIN_LED_ANT_K      PIN(B, 14)   /* вывод 53 */
#define PIN_ANT_IMON       PIN(C,  0)   /* вывод 15 */
#define PIN_V5_MON         PIN(C,  1)   /* вывод 16 */
#define PIN_V3V3_MON       PIN(C,  4)   /* вывод 32 */
#define PIN_V1V1_MON       PIN(C,  5)   /* вывод 33 */
#define PIN_SD_D0          PIN(C,  8)   /* вывод 65 */
#define PIN_SD_D1          PIN(C,  9)   /* вывод 66 */
#define PIN_SD_D2          PIN(C, 10)   /* вывод 78 */
#define PIN_SD_D3          PIN(C, 11)   /* вывод 79 */
#define PIN_SD_CLK_R       PIN(C, 12)   /* вывод 80 */
#define PIN_LED_FIX_K      PIN(C, 13)   /* вывод 7 */
#define PIN_OSC32_IN       PIN(C, 14)   /* вывод 8 */
#define PIN_OSC32_OUT      PIN(C, 15)   /* вывод 9 */
#define PIN_FMC_DA2        PIN(D,  0)   /* вывод 81 */
#define PIN_FMC_DA3        PIN(D,  1)   /* вывод 82 */
#define PIN_SD_CMD         PIN(D,  2)   /* вывод 83 */
#define PIN_FMC_NOE        PIN(D,  4)   /* вывод 85 */
#define PIN_FMC_NWE        PIN(D,  5)   /* вывод 86 */
#define PIN_FMC_NWAIT      PIN(D,  6)   /* вывод 87 */
#define PIN_FMC_NE1        PIN(D,  7)   /* вывод 88 */
#define PIN_FMC_DA13       PIN(D,  8)   /* вывод 55 */
#define PIN_FMC_DA14       PIN(D,  9)   /* вывод 56 */
#define PIN_FMC_DA15       PIN(D, 10)   /* вывод 57 */
#define PIN_GPS_SCL        PIN(D, 12)   /* вывод 59 */
#define PIN_GPS_SDA        PIN(D, 13)   /* вывод 60 */
#define PIN_FMC_DA0        PIN(D, 14)   /* вывод 61 */
#define PIN_FMC_DA1        PIN(D, 15)   /* вывод 62 */
#define PIN_FPGA_PROGRAMN  PIN(E,  2)   /* вывод 1 */
#define PIN_FPGA_INITN     PIN(E,  3)   /* вывод 2 */
#define PIN_FPGA_DONE      PIN(E,  4)   /* вывод 3 */
#define PIN_FPGA_IRQ       PIN(E,  5)   /* вывод 4 */
#define PIN_ANT_EN         PIN(E,  6)   /* вывод 5 */
#define PIN_FMC_DA4        PIN(E,  7)   /* вывод 37 */
#define PIN_FMC_DA5        PIN(E,  8)   /* вывод 38 */
#define PIN_FMC_DA6        PIN(E,  9)   /* вывод 39 */
#define PIN_FMC_DA7        PIN(E, 10)   /* вывод 40 */
#define PIN_FMC_DA8        PIN(E, 11)   /* вывод 41 */
#define PIN_FMC_DA9        PIN(E, 12)   /* вывод 42 */
#define PIN_FMC_DA10       PIN(E, 13)   /* вывод 43 */
#define PIN_FMC_DA11       PIN(E, 14)   /* вывод 44 */
#define PIN_FMC_DA12       PIN(E, 15)   /* вывод 45 */
#define PIN_MCU_CLK24      PIN(H,  0)   /* вывод 12 */

#endif

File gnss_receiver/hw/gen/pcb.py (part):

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            net = f"ADC_CLK_{LET[k]}"
            pin = next(p for p, n in self.pins[mx].items() if n == net)
            lanes[net] = (mx, pin, cx - 4.1)
        src = next((m, p) for m in self.maxes for p, n in self.pins[m].items() if n == "ADC_CLK_SRC")
        lanes["ADC_CLK_SRC"] = (src[0], src[1], CX[0] - 4.75)
        paths = {}
        for net, (mx, pin, xv) in lanes.items():
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        stub_b = 0.95 + 0.3
        # ADC_SCLK: DD5 вывод 18 -> R46 (B) -> переход -> L3 с меандром -> шарик ПЛИС
        rx, ry = P.pad_xy(dd5, next(p for p, n in pn.items() if short(n) == "ADC_SCLK_R"))
        apad = "1" if short(self.pins["R46"]["1"]) == "ADC_SCLK_R" else "2"
        bpad = "2" if apad == "1" else "1"
        g46 = P.geo(P.fps["R46"].GetFPIDAsString(), 0, "B")["pads"]
        rot46 = 0 if g46[apad][0][0] < g46[bpad][0][0] else 180      # вход резистора — ближе к DD5
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        sv = (b2[0] + 0.55, b2[1])
        self.track("ADC_SCLK", pcbnew.B_Cu, [b2, sv], 0.15)
        self.via("ADC_SCLK", *sv)
        ball = next(p for p, n in self.pins["DD7"].items() if n == "ADC_SCLK")
        bx, by = P.pad_xy("DD7", ball)
        fx, fy = P.where["DD7"][:2]
        dvx, dvy = bx + (0.4 if bx >= fx else -0.4), by + (0.4 if by >= fy else -0.4)
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
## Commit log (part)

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2025-08-21 Add technical specification for time-frequency synchronization in UAV networks
2025-08-21 Update technical specification for distributed time synchronization research
2025-08-21 Add technical specification for distributed time synchronization technology
2025-08-21 Add swarm synchronization system with core drone and algorithm modules
2025-08-21 Добавлена полная система симуляции роя дронов с PNTP синхронизацией
    - Реализован протокол PNTP (Precision Network Time Protocol)
    - Добавлены алгоритмы консенсуса и фазовой синхронизации
    - Созданы демонстрации для роев до 50 дронов
    - Реализованы 8 паттернов формаций
    - Добавлена комплексная визуализация и анализ точности
    - Создана система телеметрии и мониторинга
2025-08-23 Add web simulator for PNTP swarm with real-time WebSocket telemetry
2025-08-23 Initial commit: Drone Swarm Simulation v2.0.0 with multi-altitude flight support
2025-08-23 Добавлено управление с клавиатуры для симуляции дронов
    - Добавлены клавиши ESC, Enter, Пробел, S, R, H для управления
    - Реализована функция setupKeyboardControls() с обработкой событий
    - Добавлена подсказка о клавиатурном управлении в заголовке
    - Создана функция showKeyboardHelp() для отображения справки
    - Добавлены CSS стили для подсказки с анимацией пульсации
    - Улучшены уведомления с указанием использован
2025-08-23 Create tatus
2025-09-01 Major Update: Enhanced Mathematical Models and Repository Cleanup
    NEW FEATURES:
    - Enhanced MATH_MODEL.md with realistic drone physics and modern algorithms
    - Added MATH_EXAMPLES.md with practical formula applications
    - Created LAUNCH.md for quick start instructions
    - Updated README.md with mathematical model descriptions
    REPOSITORY CLEANUP:
